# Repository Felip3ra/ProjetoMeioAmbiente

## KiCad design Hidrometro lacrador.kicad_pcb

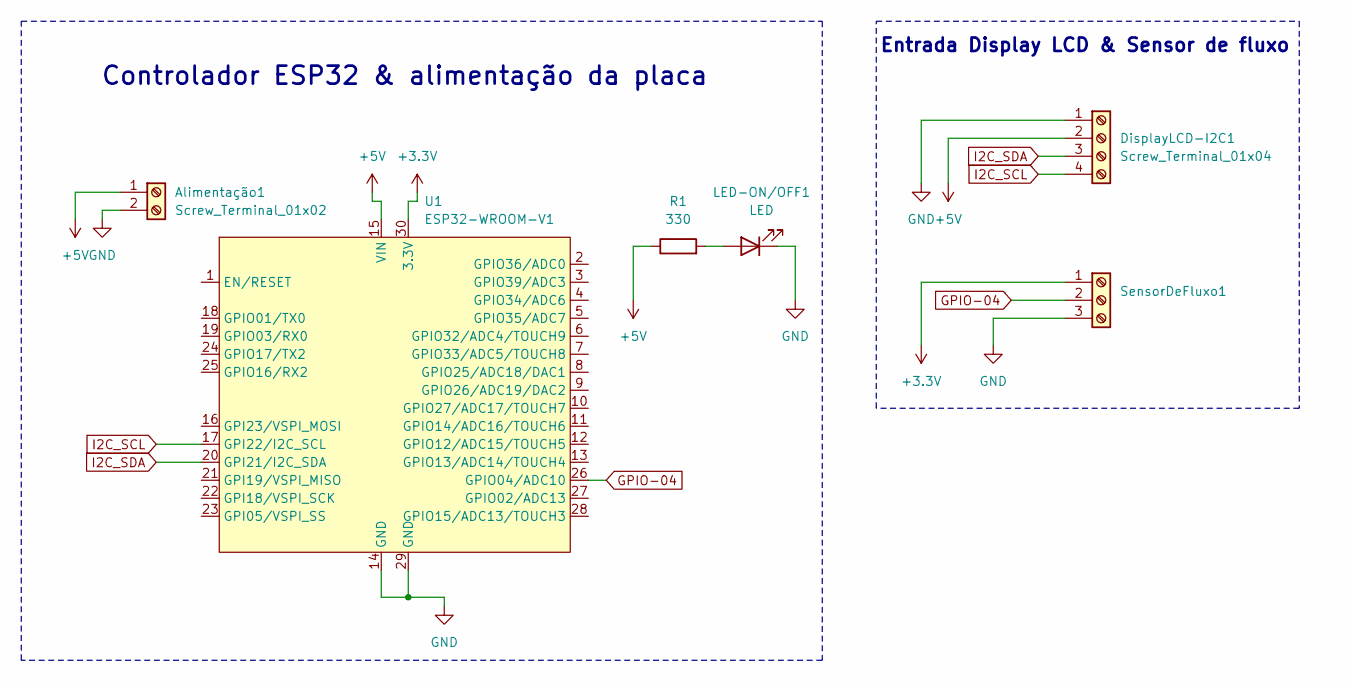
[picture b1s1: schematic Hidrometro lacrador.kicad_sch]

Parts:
Alimentação1: Screw_Terminal_01x02; TerminalBlock_Altech_AK300-2_P5.00mm
DisplayLCD-I2C1: Screw_Terminal_01x04; TerminalBlock_Altech_AK300-4_P5.00mm
LED-ON/OFF1: LED; TerminalBlock_Altech_AK300-2_P5.00mm
R1: 330; R_Axial_DIN0414_L11.9mm_D4.5mm_P20.32mm_Horizontal
SensorDeFluxo1: Screw_Terminal_01x03; TerminalBlock_Altech_AK300-3_P5.00mm
U1: ESP32-WROOM-V1; ESP32-WROOM

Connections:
+3.3V: SensorDeFluxo1.1, U1.30 (3.3V)
+5V: Alimentação1.1, DisplayLCD-I2C1.2, R1.1, U1.15 (VIN)
GND: Alimentação1.2, DisplayLCD-I2C1.1, LED-ON/OFF1.1 (K), SensorDeFluxo1.3, U1.14 (GND), U1.29 (GND)
GPIO-04: SensorDeFluxo1.2, U1.26 (GPIO04/ADC10)
I2C_SCL: DisplayLCD-I2C1.4, U1.17 (GPI22/I2C_SCL)
I2C_SDA: DisplayLCD-I2C1.3, U1.20 (GPI21/I2C_SDA)
unnamed: LED-ON/OFF1.2 (A), R1.2

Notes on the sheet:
Entrada Display LCD & Sensor de fluxo
Controlador ESP32 & alimentação da placa

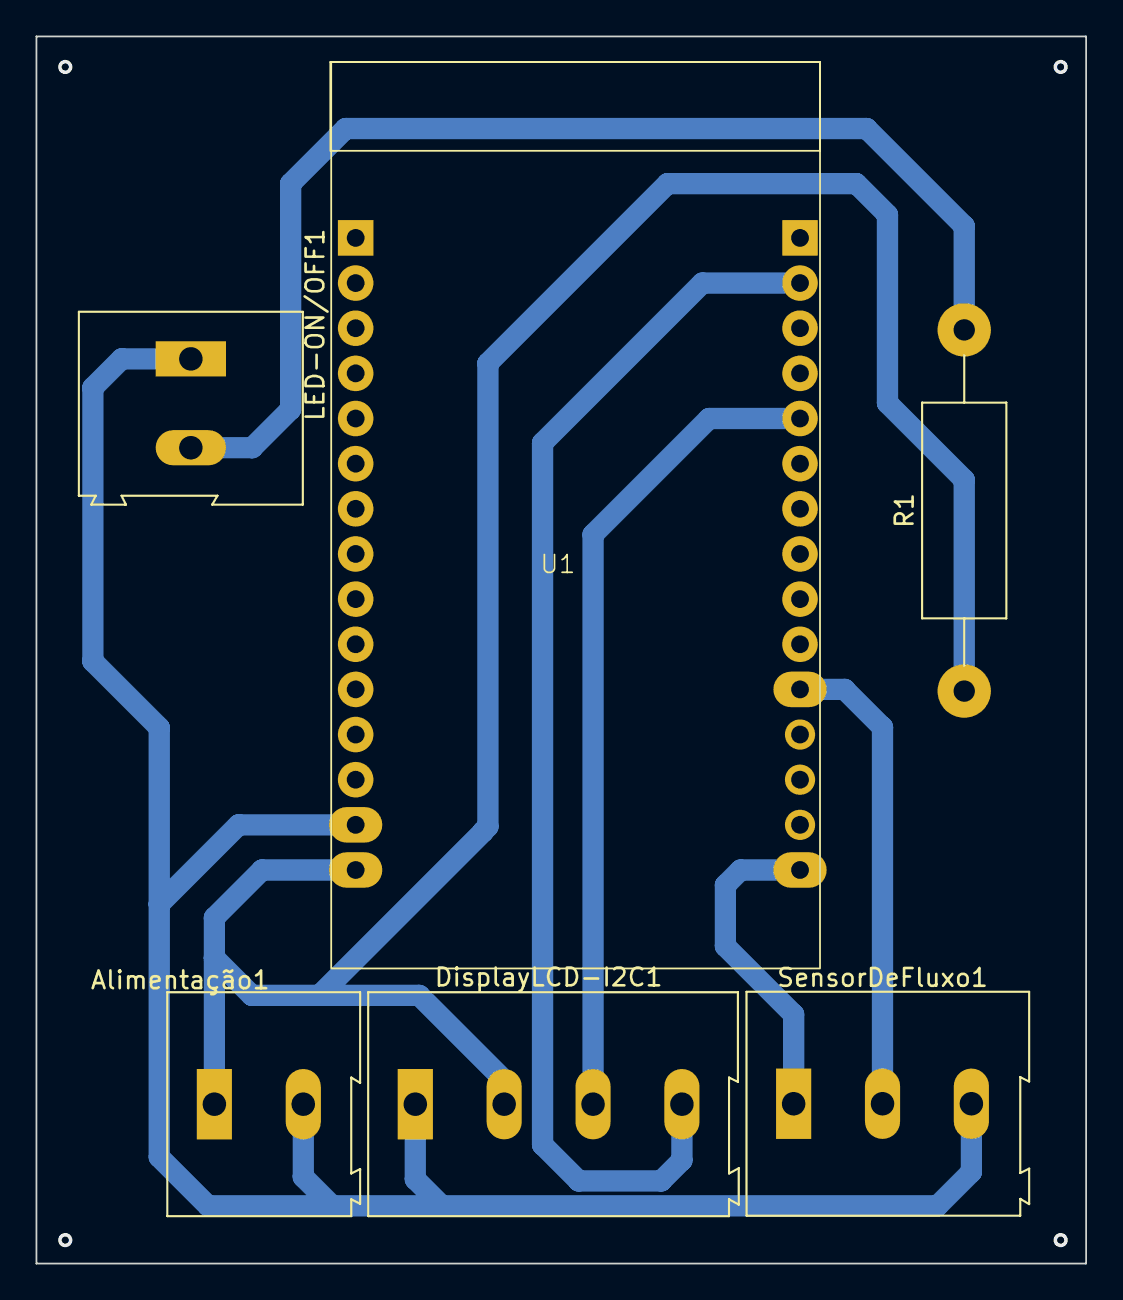
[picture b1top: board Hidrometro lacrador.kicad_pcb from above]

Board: 2 copper layers, 59.1 x 69.0 mm, 6 parts (0 on the bottom side), 7 nets.

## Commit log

2024-08-28 feat: comite_inicial
2024-08-28 feat: adicionando logo
2024-08-28 feat: adicionando campo de texto e botões
2024-08-28 feat:bottom bar e botão cadastre-se
2024-08-28 feat: tela de cadastro
2024-08-28 feat: tela de esqueceu a senha
2024-08-29 feat: tela de código
2024-08-29 feat: tela de mudar senha
2024-08-29 feat: criação parcial do widget hardware status
2024-08-29 feat: tela de home incompleta
2024-08-30 feat: tela de home completa
2024-08-30 feat: tela de connect
2024-08-30 feat: tela de perfil
2024-08-30 feat: Tela de graphs incompleta
2024-08-30 feat: mapeamento das rotas - teste
2024-09-13 fix: Alinhamento de texto do codigo de envio
2024-09-13 fix: arrumando routes
2024-09-18 feat: implementando validacao dos campos eexibicao de senha
2024-09-18 feat: implementacao da tela de recuperacao de senha html
2024-09-18 feat: configuracao com Firebase - teste
2024-09-19 feat: Cadastro com Firebase
2024-09-19 fix: dados do grafico
2024-09-19 feat: notificacao de cadastro
2024-09-19 feat: atualizacao
2024-09-20 feat: configuracao firebase
2024-09-20 fix: arrumado o erro de login após logout
2024-09-25 feat: implementação da config WI-FI ESP32
2024-09-25 feat: Remoção do campo "confirmar senha"
2024-09-25 feat: Correção das visibilidade das senhas/ implementação da troca de email e senha/implementação da recuperação de senha
2024-09-30 feat: implementação da query de buscar dados no Firebase
2024-10-01 feat: Implementação dos dados em litros obtidos pelo sensor no banco de dados
2024-10-01 fix: Correção dos Widgets averageGraph e hardwareStatus
2024-10-03 fix: Ajuste dos dados do mes
2024-10-03 Comit inicial do circuito
2024-10-04 Disposição dos componentes na PCB
2024-10-10 Finalização do circuito e da PCB
2024-10-17 mudança das portas do display LCD
2024-10-17 Adição de marcação para buracos de montagem
